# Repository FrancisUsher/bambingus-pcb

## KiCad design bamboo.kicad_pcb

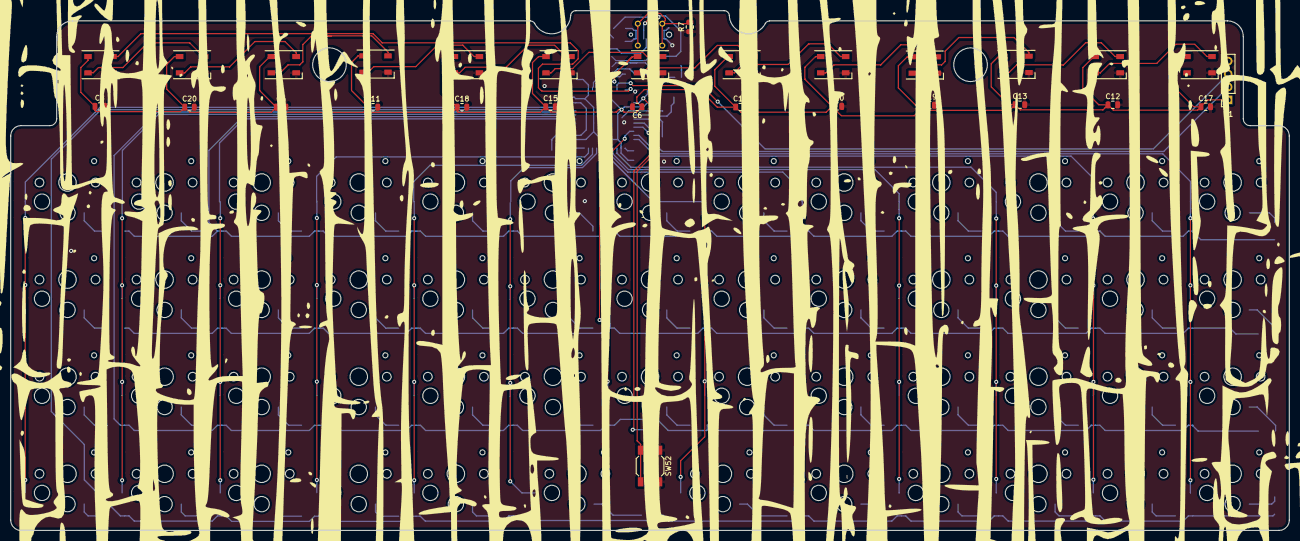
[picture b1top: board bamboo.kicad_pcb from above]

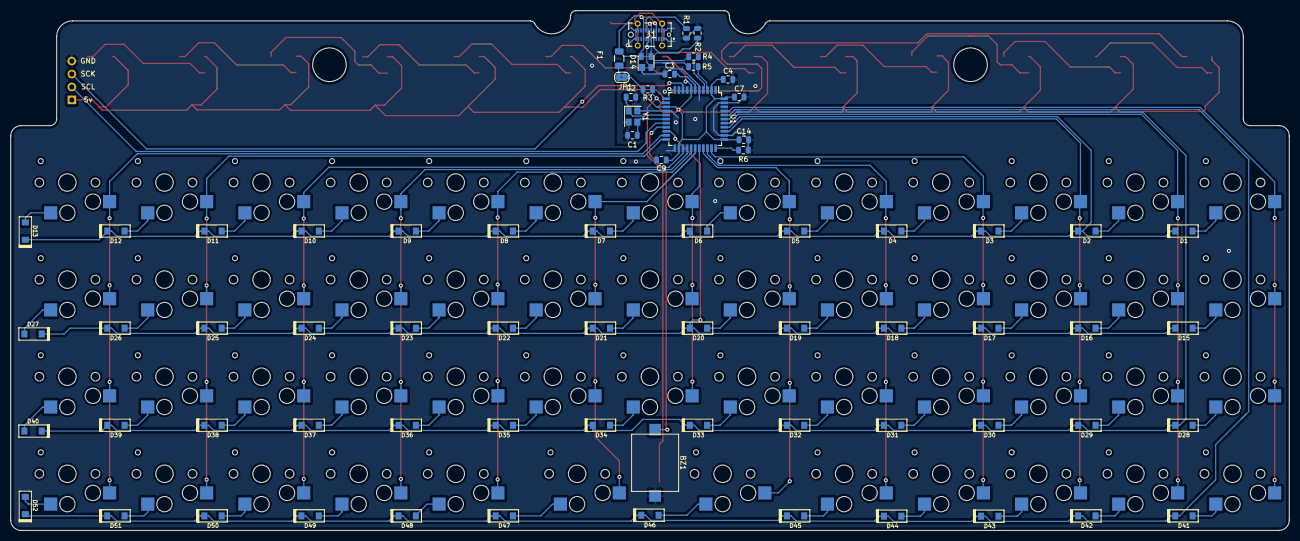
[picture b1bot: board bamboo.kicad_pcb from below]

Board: 2 copper layers, 250.9 x 102.0 mm, 152 parts (71 on the bottom side), 100 nets.

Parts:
BZ1: Buzzer; AST1109MLTRQ
C1, C2: 22pF; C_0805_2012Metric
C3: 1uF; C_0805_2012Metric
C4, C5, C6, C8, C9, C10, C11, C12, C13, C14, C15, C16, C17, C18, C19, C20: 0.1uF; C_0805_2012Metric
C7: 10uF; C_0805_2012Metric
D1, D2, D3, D4, D5, D6, D7, D8, D9, D10, D11, D12, D13, D15, D16, D17, D18, D19, D20, D21, D22, D23, D24, D25, D26, D27, D28, D29, D30, D31, D32, D33, D34, D35, D36, D37, D38, D39, D40, D41, D42, D43, D44, D45, D46, D47, D48, D49, D50, D51, D52: D_Small; D_SOD123
D14: PRTR5V0U2X; SOT-143
D53, D54, D55, D56, D57, D58, D59, D60, D61, D62, D63, D64, D65: WS2812B; LED_WS2812B_PLCC4_5.0x5.0mm_P3.2mm
F1: 500mA; Fuse_1206_3216Metric
J1: 632722110112
JP1: Jumper_NC_Small; SolderJumper-2_P1.3mm_Bridged2Bar_RoundedPad1.0x1.5mm
Null1: Blank; bamboo
P1: CONN_01X04; PinSocket_1x04_P2.54mm_Vertical
R1, R2: 5.11k; R_0805_2012Metric
R3, R6: 10k; R_0805_2012Metric
R4, R5: 22; R_0805_2012Metric
R7: 1m; R_0805_2012Metric
SW1, SW2, SW3, SW4, SW5, SW6, SW7, SW8, SW9, SW10, SW11, SW12, SW13, SW14, SW15, SW16, SW17, SW18, SW19, SW20, SW21, SW22, SW23, SW24, SW25, SW26, SW27, SW28, SW29, SW30, SW31, SW32, SW33, SW34, SW35, SW36, SW37, SW38, SW39, SW40, SW41, SW42, SW43, SW44, SW47, SW48, SW49, SW50, SW51: SW_Push; Kailh_socket_PG1350
SW45, SW46: SW_Push; Kailh_socket_PG1350_1.5
SW52: SW_Push; SW_SPST_SKQG_WithoutStem
U1: ATmega32U4-AU; TQFP-44_10x10mm_P0.8mm
Y1: 16Mhz; Crystal_SMD_3225-4Pin_3.2x2.5mm

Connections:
+5V: C4.1, C5.1, C6.1, C7.1, C8.1, C9.1, C10.1, C11.1, C12.1, C13.1, C14.1, C15.1, C16.1, C17.1, C18.1, C19.1, C20.1, D53.1, D54.1, D55.1, D56.1, D57.1, D58.1, D59.1, D60.1, D61.1, D62.1, D63.1, D64.1, D65.1, JP1.2, P1.1, R3.2, U1.2, U1.7, U1.14, U1.24, U1.34, U1.44
/D2+: R4.2, U1.4
/D2-: R5.2, U1.3
D+: D14.3, J1.A6, J1.B6, R4.1
D-: D14.2, J1.A7, J1.B7, R5.1
GND: BZ1.2, C1.1, C2.1, C3.1, C4.2, C5.2, C6.2, C7.2, C8.2, C9.2, C10.2, C11.2, C12.2, C13.2, C14.2, C15.2, C16.2, C17.2, C18.2, C19.2, C20.2, D14.1, D53.3, D54.3, D55.3, D56.3, D57.3, D58.3, D59.3, D60.3, D61.3, D62.3, D63.3, D64.3, D65.3, J1.A1, J1.A12, J1.B1, J1.B12, P1.4, R1.2, R2.1, R6.2, R7.1, SW52.1, U1.5, U1.15, U1.23, U1.35, U1.43, Y1.2, Y1.4
unnamed: C1.2, U1.17, Y1.3
unnamed: C2.2, U1.16, Y1.1
unnamed: C3.2, U1.6
unnamed: D1.2, SW1.1
unnamed: D2.2, SW2.1
unnamed: D3.2, SW3.1
unnamed: D4.2, SW4.1
unnamed: D5.2, SW5.1
unnamed: D6.2, SW6.1
unnamed: D7.2, SW7.1
unnamed: D8.2, SW8.1
unnamed: D9.2, SW9.1
unnamed: D10.2, SW10.1
unnamed: D11.2, SW11.1
unnamed: D12.2, SW12.1
unnamed: D13.2, SW13.1
unnamed: D15.2, SW14.1
unnamed: D16.2, SW15.1
unnamed: D17.2, SW16.1
unnamed: D18.2, SW17.1
unnamed: D19.2, SW18.1
unnamed: D20.2, SW19.1
unnamed: D21.2, SW20.1
unnamed: D22.2, SW21.1
unnamed: D23.2, SW22.1
unnamed: D24.2, SW23.1
unnamed: D25.2, SW24.1
unnamed: D26.2, SW25.1
unnamed: D27.2, SW26.1
unnamed: D28.2, SW27.1
unnamed: D29.2, SW28.1
unnamed: D30.2, SW29.1
unnamed: D31.2, SW30.1
unnamed: D32.2, SW31.1
unnamed: D33.2, SW32.1
unnamed: D34.2, SW33.1
unnamed: D35.2, SW34.1
unnamed: D36.2, SW35.1
unnamed: D37.2, SW36.1
unnamed: D38.2, SW37.1
unnamed: D39.2, SW38.1
unnamed: D40.2, SW39.1
unnamed: D41.2, SW40.1
unnamed: D42.2, SW41.1
unnamed: D43.2, SW42.1
unnamed: D44.2, SW43.1
unnamed: D45.2, SW44.1
unnamed: D46.2, SW45.1
unnamed: D47.2, SW46.1
unnamed: D48.2, SW47.1
unnamed: D49.2, SW48.1
unnamed: D50.2, SW49.1
unnamed: D51.2, SW50.1
unnamed: D52.2, SW51.1
unnamed: D53.2, D54.4
unnamed: D54.2, D55.4
unnamed: D55.2, D56.4
unnamed: D56.2, D57.4
unnamed: D57.2, D58.4
unnamed: D58.2, D59.4
unnamed: D59.2, D60.4
unnamed: D60.2, D61.4
unnamed: D61.2, D62.4
unnamed: D62.2, D63.4
unnamed: D63.2, D64.4
unnamed: D64.2, D65.4
unnamed: F1.1, JP1.1
unnamed: J1.A5, R2.2
unnamed: J1.B5, R1.1
unnamed: J1.MH3, J1.MH4, J1.MH5, J1.MH6, R7.2
unnamed: R3.1, SW52.2, U1.13
unnamed: R6.1, U1.33
RGB: D53.4, U1.11
SCK: P1.3, U1.9
SCL: P1.2, U1.18
Speaker: BZ1.1, U1.19
VCC: D14.4, F1.2, J1.A4, J1.A9, J1.B4, J1.B9
c0: SW1.2, SW14.2, SW27.2, SW40.2, U1.41
c1: SW2.2, SW15.2, SW28.2, SW41.2, U1.38
c2: SW3.2, SW16.2, SW29.2, SW42.2, U1.36
c3: SW4.2, SW17.2, SW30.2, SW43.2, U1.32
c4: SW5.2, SW18.2, SW31.2, SW44.2, U1.31
c5: SW6.2, SW19.2, SW32.2, SW45.2, U1.30
c6: SW7.2, SW20.2, SW33.2, U1.29
c7: SW8.2, SW21.2, SW34.2, SW46.2, U1.28
c8: SW9.2, SW22.2, SW35.2, SW47.2, U1.27
c9: SW10.2, SW23.2, SW36.2, SW48.2, U1.26
c10: SW11.2, SW24.2, SW37.2, SW49.2, U1.25
c11: SW12.2, SW25.2, SW38.2, SW50.2, U1.22
c12: SW13.2, SW26.2, SW39.2, SW51.2, U1.21
r0: D1.1, D2.1, D3.1, D4.1, D5.1, D6.1, D7.1, D8.1, D9.1, D10.1, D11.1, D12.1, D13.1, U1.37
r1: D15.1, D16.1, D17.1, D18.1, D19.1, D20.1, D21.1, D22.1, D23.1, D24.1, D25.1, D26.1, D27.1, U1.20
r2: D28.1, D29.1, D30.1, D31.1, D32.1, D33.1, D34.1, D35.1, D36.1, D37.1, D38.1, D39.1, D40.1, U1.39
r3: D41.1, D42.1, D43.1, D44.1, D45.1, D46.1, D47.1, D48.1, D49.1, D50.1, D51.1, D52.1, U1.40

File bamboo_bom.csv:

"Id";"Designator";"Package";"Quantity";"Designation";"Supplier and ref";
1;"SW52";"SW_SPST_SKQG_WithoutStem";1;"SW_Push";;;
2;"J1";"632722110112";1;"632722110112";;;
3;"R7";"R_0805_2012Metric";1;"1m";;;
4;"D14";"SOT-143";1;"PRTR5V0U2X";;;
5;"R1,R2";"R_0805_2012Metric";2;"5.11k";;;
6;"Null2";"Hitoto2";1;"Blank";;;
7;"Null1";"bamboo";1;"Blank";;;
8;"Y1";"Crystal_SMD_3225-4Pin_3.2x2.5mm";1;"16Mhz";;;
9;"P1";"PinSocket_1x04_P2.54mm_Vertical";1;"CONN_01X04";;;
10;"JP1";"SolderJumper-2_P1.3mm_Bridged2Bar_RoundedPad1.0x1.5mm";1;"Jumper_NC_Small";;;
11;"BZ1";"AST1109MLTRQ";1;"Buzzer";;;
12;"D58,D53,D54,D55,D56,D57,D60,D61,D63,D62,D64,D65,D59";"LED_WS2812B_PLCC4_5.0x5.0mm_P3.2mm";13;"WS2812B";;;
13;"D16,D38,D36,D35,D34,D33,D32,D31,D30,D29,D28,D20,D37,D48,D49,D50,D51,D52,D45,D44,D43,D42,D41,D40,D46,D26,D39,D12,D10,D9,D8,D7,D6,D5,D4,D3,D2,D27,D11,D21,D22,D23,D24,D47,D19,D18,D17,D15,D25,D1,D13";"D_SOD123";51;"D_Small";;;
14;"C19,C18,C17,C16,C15,C14,C13,C12,C11,C20,C9,C8,C10,C4,C5,C6";"C_0805_2012Metric";16;"0.1uF";;;
15;"SW5,SW27,SW28,SW29,SW30,SW31,SW32,SW33,SW34,SW35,SW36,SW37,SW25,SW40,SW41,SW42,SW43,SW44,SW48,SW49,SW50,SW51,SW1,SW13,SW38,SW2,SW3,SW4,SW6,SW7,SW8,SW9,SW10,SW11,SW12,SW47,SW14,SW15,SW16,SW17,SW18,SW19,SW20,SW21,SW22,SW23,SW24,SW39,SW26";"Kailh_socket_PG1350";49;"SW_Push";;;
16;"SW45,SW46";"Kailh_socket_PG1350_1.5";2;"SW_Push";;;
17;"C1,C2";"C_0805_2012Metric";2;"22pF";;;
18;"C3";"C_0805_2012Metric";1;"1uF";;;
19;"C7";"C_0805_2012Metric";1;"10uF";;;
20;"F1";"Fuse_1206_3216Metric";1;"500mA";;;
21;"U1";"TQFP-44_10x10mm_P0.8mm";1;"ATmega32U4-AU";;;
22;"R3,R6";"R_0805_2012Metric";2;"10k";;;
23;"R5,R4";"R_0805_2012Metric";2;"22";;;

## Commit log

2021-01-07 Add PCB files
